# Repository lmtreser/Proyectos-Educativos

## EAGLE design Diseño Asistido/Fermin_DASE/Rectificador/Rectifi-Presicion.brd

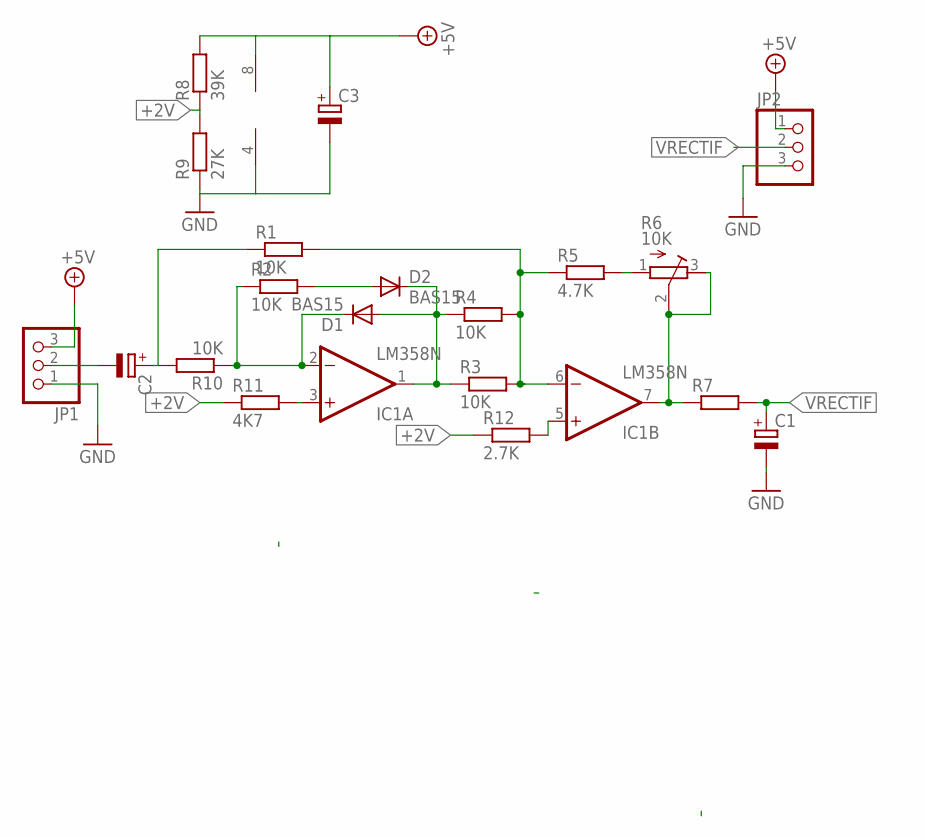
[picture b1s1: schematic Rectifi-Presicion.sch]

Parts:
C1, C2: CPOL-EUE2.5-5; E2,5-5
C3: CPOL-EUE2.5-6; E2,5-6
D1, D2: BAS15; DO34-7
IC1: LM358N; DIL08
JP1, JP2: PINHD-1X3; 1X03
R1, R2, R3, R4, R10: 10K; 0207/7
R5: 4.7K; 0207/7
R6: 10K; RTRIM64W
R7: R-EU_0207/7; 0207/7
R8: 39K; 0207/7
R9: 27K; 0207/7
R11: 4K7; 0207/7
R12: 2.7K; 0207/7

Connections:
+2V: R8.1, R9.2, R11.1, R12.1
+5V: C3.+, IC1.8 (V+), JP1.3, JP2.1, R8.2
GND: C1.-, C3.-, IC1.4 (V-), JP1.1, JP2.3, R9.1
unnamed: D1.A, D2.C, IC1.1 (OUT), R3.1, R4.1
unnamed: C2.+, R1.1, R10.2
unnamed: R5.2, R6.1 (A)
unnamed: D2.A, R2.2
unnamed: IC1.6 (-IN), R1.2, R3.2, R4.2, R5.1
unnamed: D1.C, IC1.2 (-IN), R2.1, R10.1
unnamed: IC1.7 (OUT), R6.2 (S), R6.3 (E), R7.1
unnamed: C2.-, JP1.2
unnamed: IC1.5 (+IN), R12.2
VPOL: IC1.3 (+IN), R11.2
VRECTIF: C1.+, JP2.2, R7.2

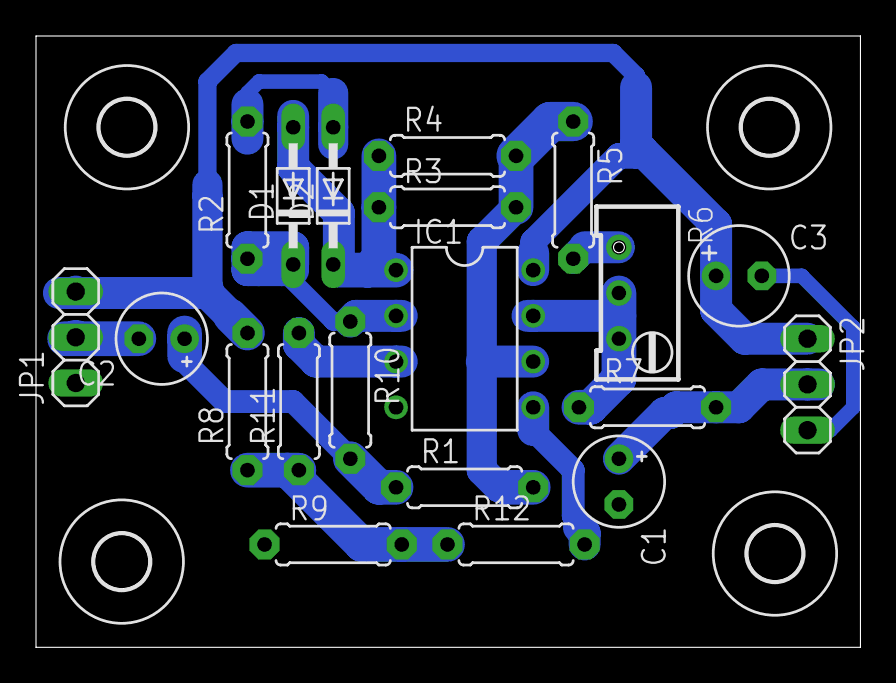
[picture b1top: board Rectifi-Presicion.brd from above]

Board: 2 copper layers, 45.8 x 34.0 mm, 24 parts (0 on the bottom side), 14 nets.

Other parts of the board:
U$1, U$2, U$3, U$4: 3,0

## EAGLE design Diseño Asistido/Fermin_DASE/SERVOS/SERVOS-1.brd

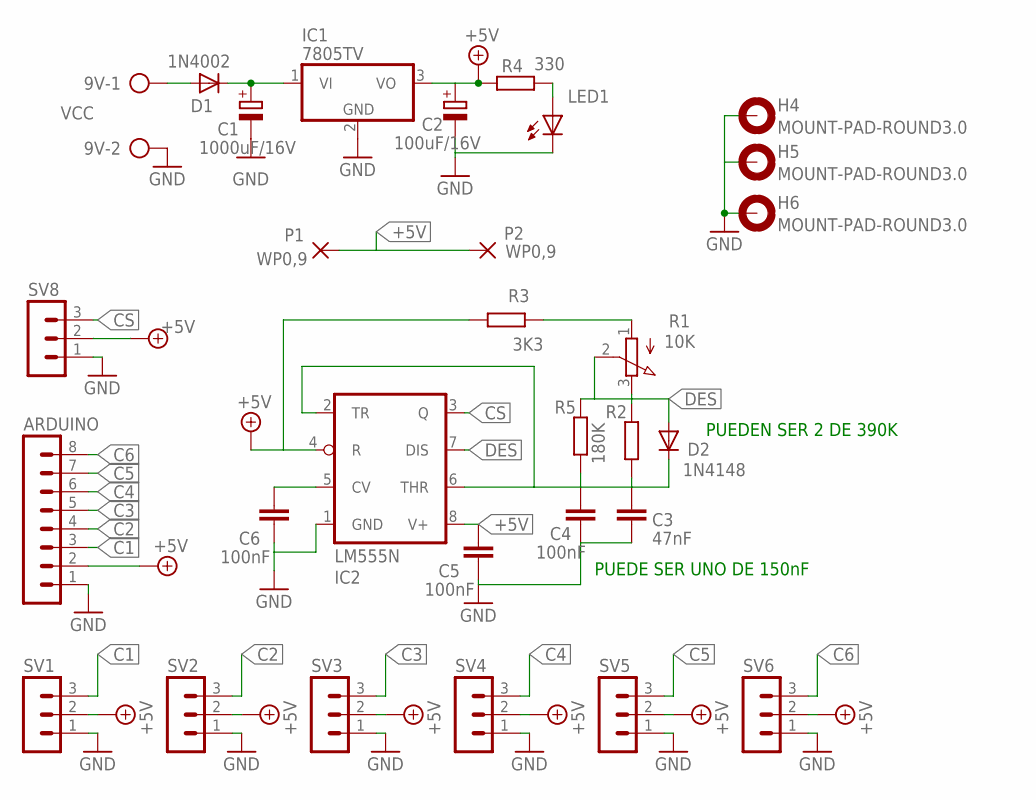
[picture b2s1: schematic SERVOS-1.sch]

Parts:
9V: VCC; AK500/2
ARDUINO: MA08-1
C1: 1000uF/16V; E2,5-7
C2: 100uF/16V; E2,5-5
C3: 47nF; C050-025X075
C4, C5, C6: 100nF; C050-025X075
D1: 1N4002; DO35-7
D2: 1N4148; DO35-7
H4, H5, H6: MOUNT-PAD-ROUND3.0; 3,0-PAD
IC1: 7805TV; TO220V
IC2: LM555N; DIL08
LED1: LED3MM
P1, P2: WP0,9; 1,6/0,9
R1: 10K; 3RP/1610N
R2: R-EU_0207/10; 0207/10
R3: 3K3; 0207/10
R4: 330; 0207/10
R5: 180K; 0207/10
SV1, SV2, SV3, SV4, SV5, SV6, SV8: MA03-1

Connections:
+5V: ARDUINO.2, C2.+, C5.1, IC1.3 (VO), IC2.4 (R), IC2.8 (V+), P1.1, P2.1, R3.2, R4.1, SV1.2, SV2.2, SV3.2, SV4.2, SV5.2, SV6.2, SV8.2
C1: ARDUINO.3, SV1.3
C2: ARDUINO.4, SV2.3
C3: ARDUINO.5, SV3.3
C4: ARDUINO.6, SV4.3
C5: ARDUINO.7, SV5.3
C6: ARDUINO.8, SV6.3
CS: IC2.3 (Q), SV8.3
DES: D2.A, IC2.7 (DIS), R1.2 (S), R1.3 (E), R2.2, R5.2
GND: 9V.2, ARDUINO.1, C1.-, C2.-, C3.2, C4.2, C5.2, C6.2, H4.B3,0, H5.B3,0, H6.B3,0, IC1.2 (GND), IC2.1 (GND), LED1.K (C), SV1.1, SV2.1, SV3.1, SV4.1, SV5.1, SV6.1, SV8.1
unnamed: C1.+, D1.C, IC1.1 (VI)
unnamed: 9V.1, D1.A
unnamed: LED1.A, R4.2
unnamed: C6.1, IC2.5 (CV)
unnamed: R1.1 (A), R3.1
unnamed: C3.1, C4.1, D2.C, IC2.2 (TR), IC2.6 (THR), R2.1, R5.1

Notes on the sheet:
PUEDE SER UNO DE 150nF
PUEDEN SER 2 DE 390K

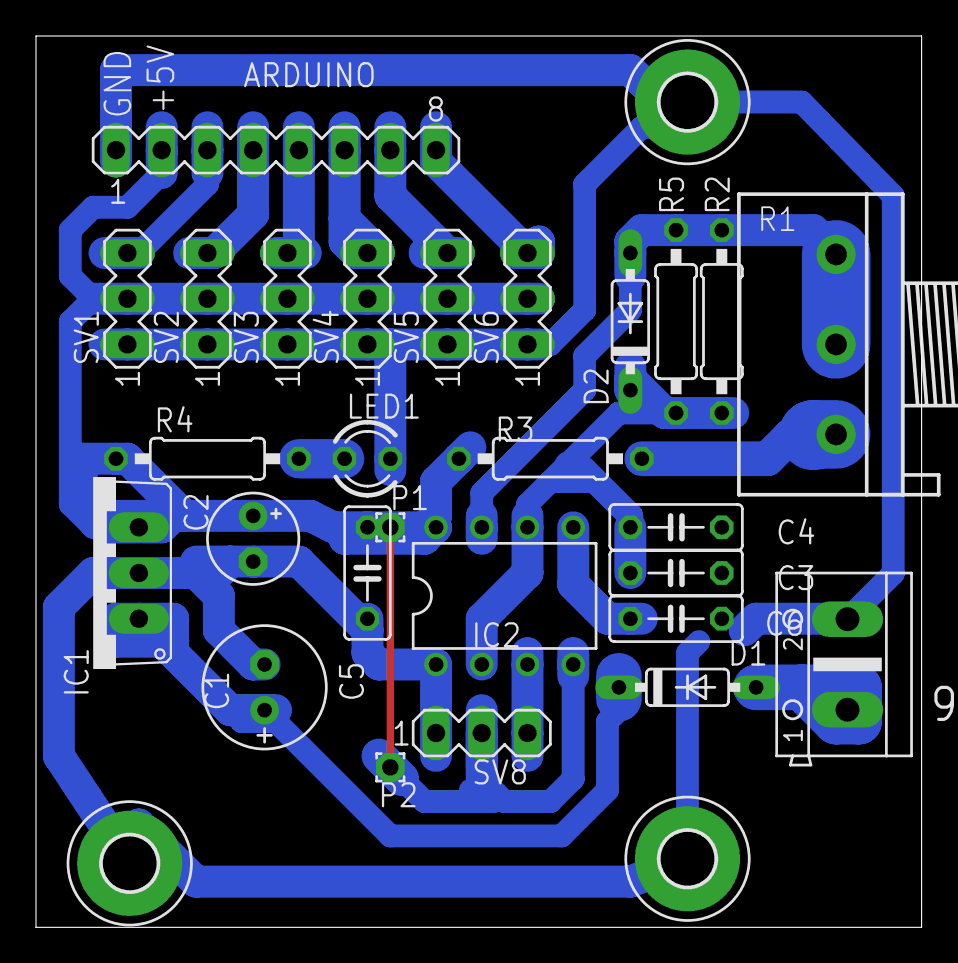
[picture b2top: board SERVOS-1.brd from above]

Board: 2 copper layers, 49.2 x 49.5 mm, 30 parts (0 on the bottom side), 16 nets.

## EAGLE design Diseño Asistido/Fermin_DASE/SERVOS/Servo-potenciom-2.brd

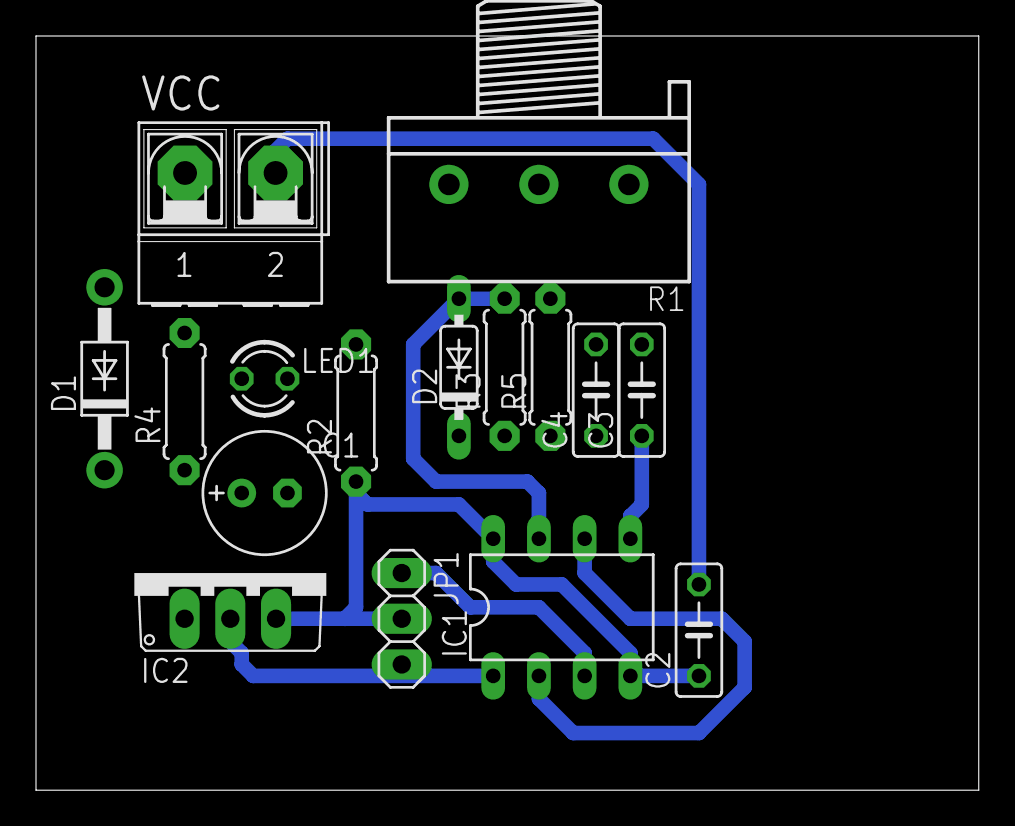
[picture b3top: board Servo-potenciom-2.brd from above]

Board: 2 copper layers, 52.4 x 41.9 mm, 16 parts (0 on the bottom side), 10 nets.

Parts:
C1: 220uF/16V; E2,5-7
C2, C4: 100nF; C050-025X075
C3: 10nF; C050-025X075
D1: 1N4004; DO41-10
D2: 1N4148DO35-7; DO35-7
IC1: NE555; DIL-08
IC2: 7805TV; TO220V
JP1: SERVO; 1X03
LED1: ROJO; LED3MM
R1: 10K; 3RP/1610N
R2: 10K; 0207/7
R3, R5: 390K; 0207/7
R4: 1K; 0207/7
VCC: +12V; AK500/2-H

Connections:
+5V: C2.1, IC1.4, IC1.8, IC2.3, JP1.2, R2.1
GND: C1.-, C2.2, C3.2, C4.2, IC1.1, IC2.2, JP1.3, LED1.K, VCC.2
unnamed: D1.A, VCC.1
unnamed: C1.+, D1.C, IC2.1, R4.1
unnamed: IC1.3, JP1.1
unnamed: C3.1, IC1.5
unnamed: R1.3, R2.2
unnamed: D2.A, IC1.7, R1.1, R1.2, R3.2, R5.2
unnamed: C4.1, D2.C, IC1.2, IC1.6, R3.1, R5.1
unnamed: LED1.A, R4.2

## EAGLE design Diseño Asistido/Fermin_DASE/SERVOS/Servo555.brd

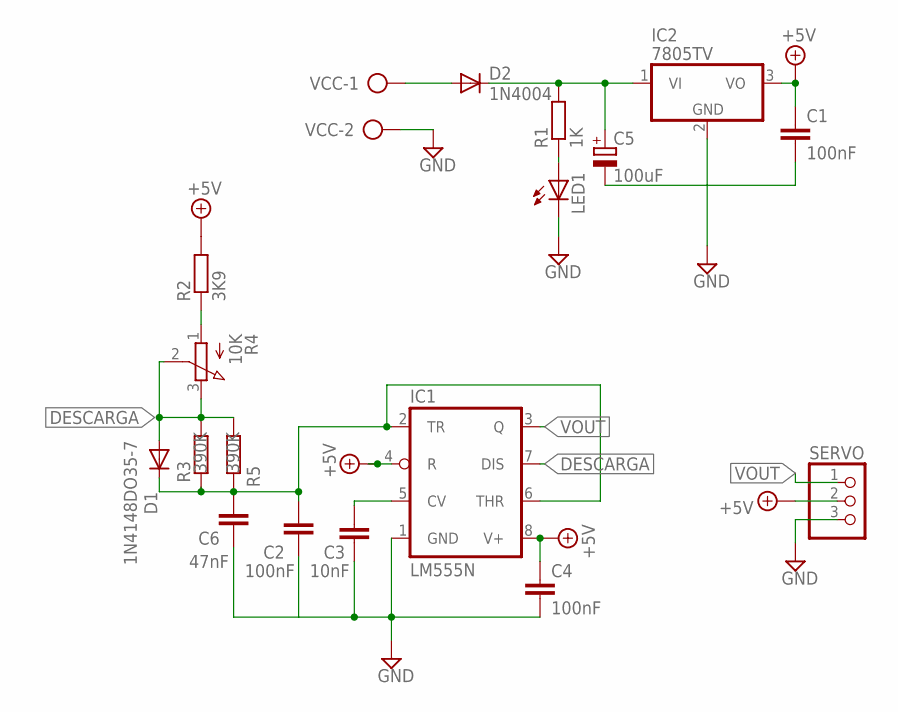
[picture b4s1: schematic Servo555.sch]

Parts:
C1, C2, C4: 100nF; C050-025X075
C3: 10nF; C050-025X075
C5: 100uF; E2,5-7
C6: 47nF; C050-025X075
D1: 1N4148DO35-7; DO35-7
D2: 1N4004; DO41-10
IC1: LM555N; DIL08
IC2: 7805TV; TO220V
LED1: LED3MM
R1: 1K; 0207/7
R2: 3K9; 0207/7
R3, R5: 390K; 0207/7
R4: 10K; 3RP/1610N
SERVO: PINHD-1X3; 1X03
VCC: AK500/2

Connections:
+5V: C1.1, C4.1, IC1.4 (R), IC1.8 (V+), IC2.3 (VO), R2.2, SERVO.2
DESCARGA: D1.A, IC1.7 (DIS), R3.2, R4.2 (S), R4.3 (E), R5.2
GND: C1.2, C2.2, C3.2, C4.2, C5.-, C6.2, IC1.1 (GND), IC2.2 (GND), LED1.K (C), SERVO.3, VCC.2
unnamed: D2.A, VCC.1
unnamed: C5.+, D2.C, IC2.1 (VI), R1.2
unnamed: LED1.A, R1.1
unnamed: C2.1, C6.1, D1.C, IC1.2 (TR), IC1.6 (THR), R3.1, R5.1
unnamed: C3.1, IC1.5 (CV)
unnamed: R2.1, R4.1 (A)
VOUT: IC1.3 (Q), SERVO.1

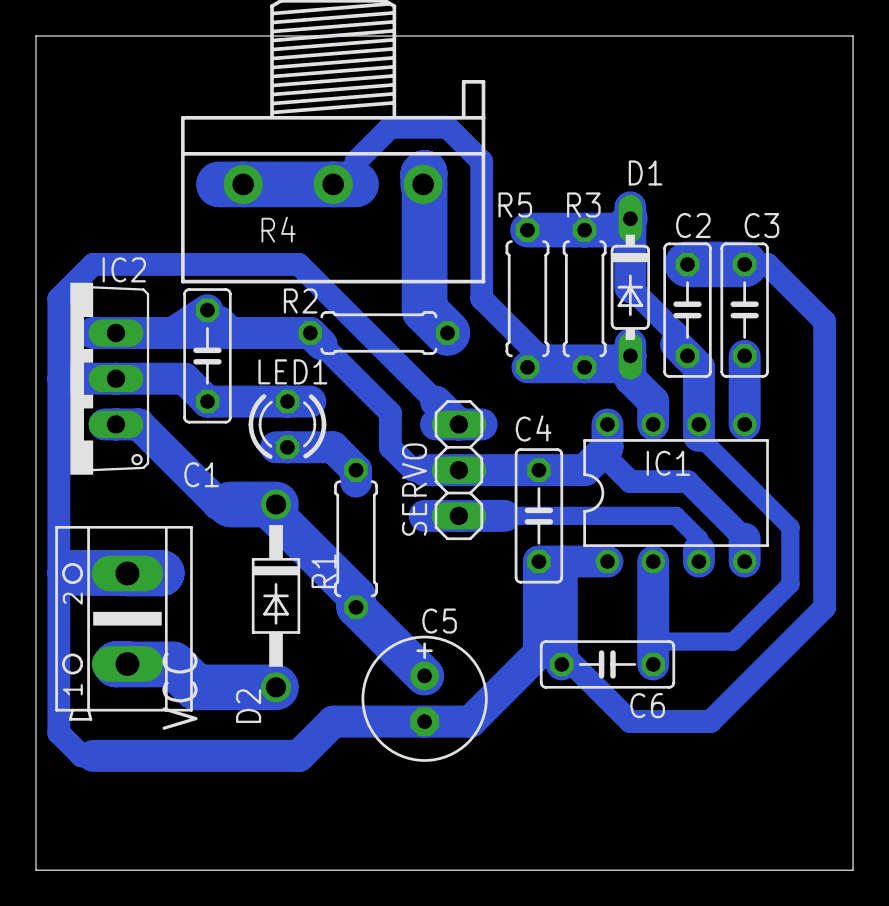
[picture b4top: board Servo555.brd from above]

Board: 2 copper layers, 45.4 x 46.3 mm, 18 parts (0 on the bottom side), 10 nets.

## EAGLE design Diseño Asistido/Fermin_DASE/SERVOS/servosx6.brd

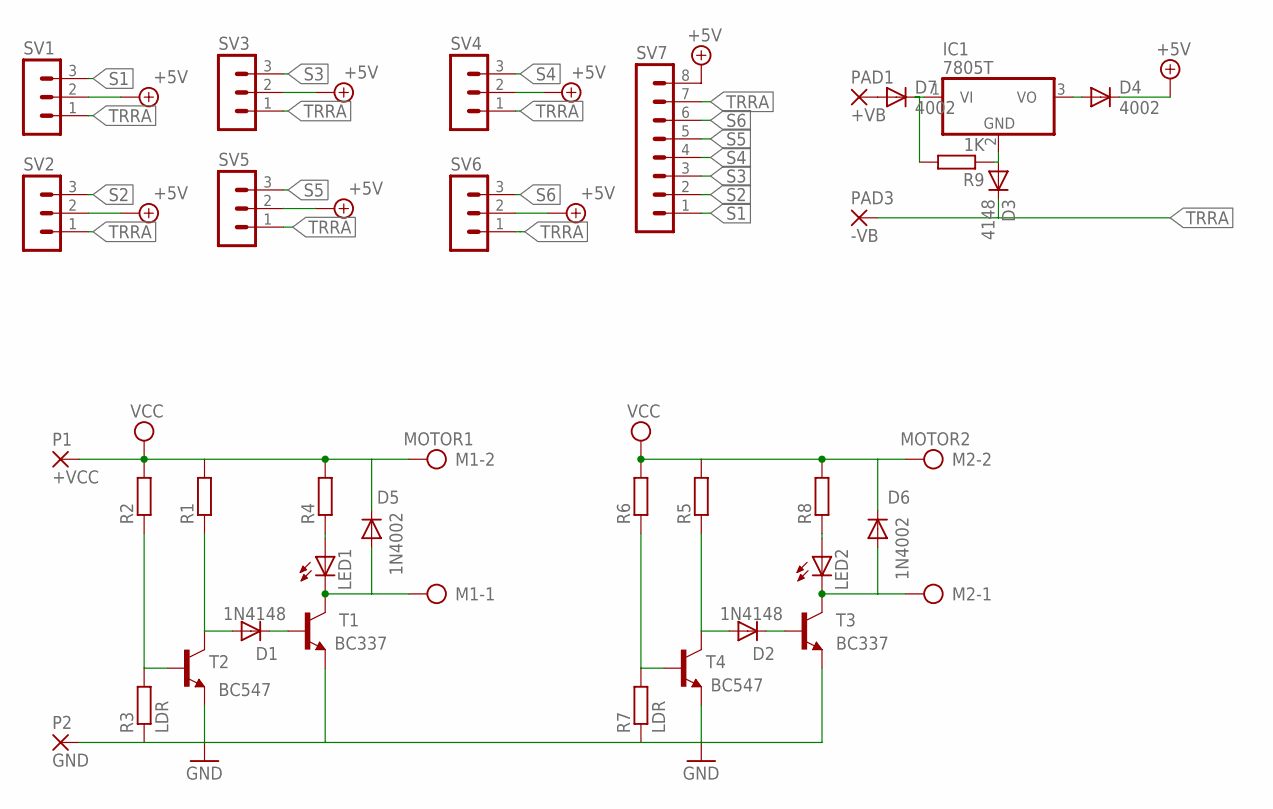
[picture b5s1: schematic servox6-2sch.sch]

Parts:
D1, D2: 1N4148; DO35-7
D3: 4148; DO35-7
D4, D7: 4002; DO35-7
D5, D6: 1N4002; DO41-10
IC1: 7805T; TO220H
LED1, LED2: LED3MM
M1: MOTOR1; AK500/2
M2: MOTOR2; AK500/2
P1: +VCC; 2,15/1,0
P2: GND; 2,15/1,0
PAD1: +VB; 1,6/0,9
PAD3: -VB; 1,6/0,9
R1, R2, R4, R5, R6, R8: R-EU_0207/7; 0207/7
R3, R7: LDR; 0204/5
R9: 1K; 0207/7
SV1, SV2, SV3, SV4, SV5, SV6: MA03-1
SV7: MA08-1
T1, T3: BC337; TO92-CBE
T2, T4: BC547; TO92-CBE

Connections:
+5V: D4.C, SV1.2, SV2.2, SV3.2, SV4.2, SV5.2, SV6.2, SV7.8
GND: P2.1, R3.1, R7.1, T1.E, T2.E, T3.E, T4.E
unnamed: D1.C, T1.B
unnamed: D1.A, R1.1, T2.C
unnamed: D5.A, LED1.K (C), M1.1, T1.C
unnamed: D3.A, IC1.2 (GND), R9.1
unnamed: LED1.A, R4.1
unnamed: R2.1, R3.2, T2.B
unnamed: D2.C, T3.B
unnamed: D2.A, R5.1, T4.C
unnamed: D6.A, LED2.K (C), M2.1, T3.C
unnamed: D4.A, IC1.3 (VO)
unnamed: R6.1, R7.2, T4.B
unnamed: LED2.A, R8.1
unnamed: D7.C, IC1.1 (VI), R9.2
unnamed: D7.A, PAD1.1
S1: SV1.3, SV7.1
S2: SV2.3, SV7.2
S3: SV3.3, SV7.3
S4: SV4.3, SV7.4
S5: SV5.3, SV7.5
S6: SV6.3, SV7.6
TRRA: D3.C, PAD3.1, SV1.1, SV2.1, SV3.1, SV4.1, SV5.1, SV6.1, SV7.7
VCC: D5.C, D6.C, M1.2, M2.2, P1.1, R1.2, R2.2, R4.2, R5.2, R6.2, R8.2

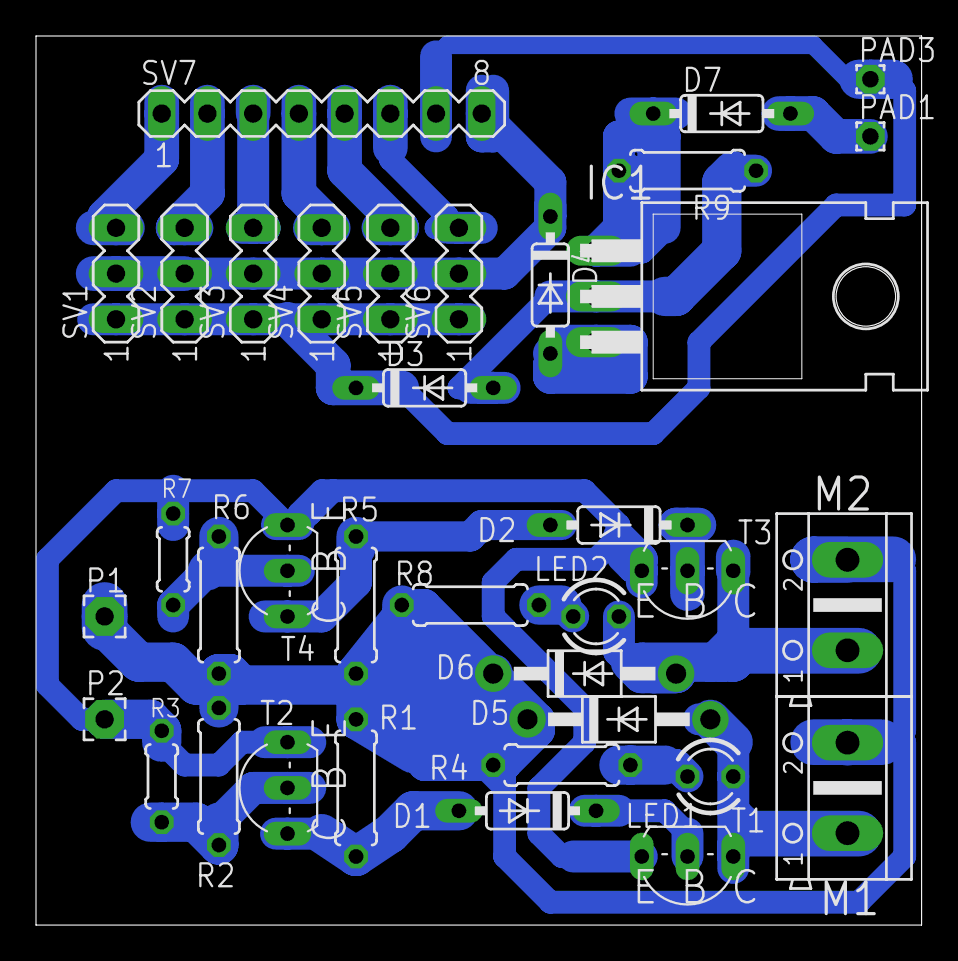
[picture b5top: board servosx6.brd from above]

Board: 2 copper layers, 49.2 x 49.4 mm, 36 parts (0 on the bottom side), 24 nets.
